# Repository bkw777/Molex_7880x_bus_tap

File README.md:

# Molex 7880x BUS TAP
Bus tap to fit between a Molex 78805 socket and a chip in a Molex 78802 carrier

More pics: https://photos.app.goo.gl/PHQ1rTQFpPRF6NSh8

Provides a connection point for a logic analyzer or oscilloscope to tap the bus between a Molex 78805 socket and a mating Molex 78802 carrier module that would normally be in the socket.

## Parts

Carrier for the small PCB: https://github.com/bkw777/Molex78802_Module/blob/master/Carrier/Molex78802_PCB_28.stl  
&nbsp;&nbsp;Some places to buy from. Select Material: Nylon, Process: SLS or MJF  
&nbsp;&nbsp;https://www.sculpteo.com/en/print/molex78802_pcb_28-18/nC7YgK6X  
&nbsp;&nbsp;https://www.pcbway.com/project/shareproject/Molex_7880x_28_PCB_Carrier_9419cd9c.html

Housing for the large PCB: [CASE/Molex_7880x_bus_tap_cover.stl](CASE/Molex_7880x_bus_tap_cover.stl)  
&nbsp;&nbsp;This one can be FDM printed.

FFC connector (x2): https://www.digikey.com/en/products/detail/amphenol-cs-fci/F52R-1A7H1-11028/11564624

FFC cable - 4" gold - Molex 0150390449 : https://www.digikey.com/en/products/detail/molex/0150390449/11581605  
FFC Cable - 6" gold - Molex 0150390453 : https://www.digikey.com/en/products/detail/molex/0150390453/11581883  
Other FFC Cables in other lengths, copper weight, plating options: https://www.digikey.com/short/pqq5pd04  

Molex 78805 socket: These are no longer made. Find me on the M100 mail list. I have some and will sell them one at a time until gone.  

Other possible solutions for the socket:  
* Once in a great while they do turn up on ebay or other places on-line:  
  https://www.dhgate.com/product/for-molex-dip28p-ic-chip-socket-silver-plated/835617844.html  
  https://www.ebay.com/itm/153988317907  
  Search "molex ic socket" and then ignore all the normal dip sockets.  
  Other search terms: 8878 28S, A78805-0518, A78805-0918, 15-29-9282, 15-41-2283  
  Or any other part number from here: https://github.com/bkw777/Molex78802_Module/blob/master/references/015299282_sd_corrected.pdf  
  Particularly detail-1, detail-10, detail-11 as those ones all have key slots at positions 1,5,9. The peg positions on the bottom don't matter because they can just be cut off.  
  (Or maybe I'll update the pcb to include drill holes in all 8 peg positions. Really any version of the socket would be better than nothing if you found any at all, just cut the missing key slots if needed.)  
* DIP-28 (or more) test clip and a standard dip-28 socket or male pin headers to connect the wires.  
  When searching for a test clip, make sure it opens wide enough for 600 mill / aka 0.6" wide dip-28, not just 300 mil.  
  https://duckduckgo.com/?t=h_&q=test+clip+dip+28+32+40+600+0.6
* Solder long wire-wrap pins in place of the socket and wedge the module between the pins.  
  https://www.digikey.com/en/products/detail/samtec-inc/ZW-16-15-F-S-225-175/6614101  
  The width of the module is a little wider than the width of the pins, so the pins would need to be bent, or change the PCB to provide a footprint with just the right spacing.  
* Change the PCB to use 2 of these: https://www.digikey.com/en/products/detail/samtec-inc/SIR1-15-L-S/10218718  
* Change the PCB to use these: https://lectronz.com/products/flexypin-pack-of-100

TODO: Design a socket that can be printed and just needs plain wire for the contacts.

Machines with this socket:  
* TRS-80/TANDY Model 100, 102, 200, 600
* Kyotronic KC-85
* Epson PX-4, PX-8
* Intermec 9440, Telexon 710, and similar hand-held teriminals
* Allen-Bradley SLC 500 programmable controllers

Cable notes:  
4" is long enough to reach out from under the nearest side to the socket on all machines.  
6" is long enough to reach the left instead of the front on a Model 200.  
8" is long enough to reach the back on a Model 100, and does still work, but might be getting marginal at this length.  
10" untested  
12" does not work

# PINOUTS
<table>
<tr> <th colspan=4>TANDY 100/102/200</th> <th width=100></th> <th colspan=4>TANDY 600 / Epson PX-4/8<br>(STANDARD MASK ROM)</th> </tr>
<tr> <td>VCC</td><td>1</td><td>28</td><td>A14</td> <td></td>  <td>NC</td><td>1</td><td>28</td><td>VCC</td> </tr>
<tr> <td>A10</td><td></td><td></td><td>/CS</td> <td></td>  <td>A12</td><td></td><td></td><td>A14</td> </tr>
<tr> <td>A7</td><td></td><td></td><td>A8</td> <td></td>  <td>A7</td><td></td><td></td><td>A13</td> </tr>
<tr> <td>A6</td><td></td><td></td><td>A9</td> <td></td>  <td>A6</td><td></td><td></td><td>A8</td> </tr>
<tr> <td>A5</td><td></td><td></td><td>A12</td> <td></td>  <td>A5</td><td></td><td></td><td>A9</td> </tr>
<tr> <td>A4</td><td></td><td></td><td>ALE</td> <td></td>  <td>A4</td><td></td><td></td><td>A11</td> </tr>
<tr> <td>A3</td><td></td><td></td><td>A13</td> <td></td>  <td>A3</td><td></td><td></td><td>/OE</td> </tr>
<tr> <td>A2</td><td></td><td></td><td>/OE</td> <td></td>  <td>A2</td><td></td><td></td><td>A10</td> </tr>
<tr> <td>A1</td><td></td><td></td><td>A11</td> <td></td>  <td>A1</td><td></td><td></td><td>/CS</td> </tr>
<tr> <td>A0</td><td></td><td></td><td>AD7</td> <td></td>  <td>A0</td><td></td><td></td><td>D7</td> </tr>
<tr> <td>AD0</td><td></td><td></td><td>AD6</td> <td></td>  <td>D0</td><td></td><td></td><td>D6</td> </tr>
<tr> <td>AD1</td><td></td><td></td><td>AD5</td> <td></td>  <td>D1</td><td></td><td></td><td>D5</td> </tr>
<tr> <td>AD2</td><td></td><td></td><td>AD4</td> <td></td>  <td>D2</td><td></td><td></td><td>D4</td> </tr>

<tr> <td>GND</td><td>14</td><td>15</td><td>AD3</td> <td></td>  <td>GND</td><td>14</td><td>15</td><td>D3</td> </tr>
</table>
<!--
|     |     |     |     |     |     |     |     |     |     |
| --- | --- | --- | --- | --- | --- | --- | --- | --- | --- |
| VCC | 1   | 28  | A14 |     |     | NC  | 1   | 28  | VCC |
| A10 |     |     | /CS |     |     | A12 |     |     | A14 |
| A7  |     |     | A8  |     |     | A7  |     |     | A13 |
| A6  |     |     | A9  |     |     | A6  |     |     | A8  |
| A5  |     |     | A12 |     |     | A5  |     |     | A9  |
| A4  |     |     | ALE |     |     | A4  |     |     | A11 |
| A3  |     |     | A13 |     |     | A3  |     |     | /OE |
| A2  |     |     | /OE |     |     | A2  |     |     | A10 |
| A1  |     |     | A11 |     |     | A1  |     |     | /CS |
| A0  |     |     | AD7 |     |     | A0  |     |     | D7  |
| AD0 |     |     | AD6 |     |     | D0  |     |     | D6  |
| AD1 |     |     | AD5 |     |     | D1  |     |     | D5  |
| AD2 |     |     | AD4 |     |     | D2  |     |     | D4  |
| GND | 14  | 15  | AD3 |     |     | GND | 14  | 15  | D3  |
-->

# GND pins work-around
This thing could really use a bunch more GND pins, both for logic analyzer probes and for a place to clip oscilloscope probe alligator clips.
Currently there is only the single GND pin which is pin 14.

For now a simple work-around that provides both extra pins for logic analyzer probe grounds and a perfect place for a scope probe alligator clip, is just a piece of single row male pin header with a wire soldered to bridge all of the posts, and a single short female-female dupont jumper to connect to the single gnd pin.

# Related
http://tandy.wiki/Molex78802_Module  
https://github.com/bkw777/M4ROM  
http://tandy.wiki/Teeprom  
http://tandy.wiki/REX

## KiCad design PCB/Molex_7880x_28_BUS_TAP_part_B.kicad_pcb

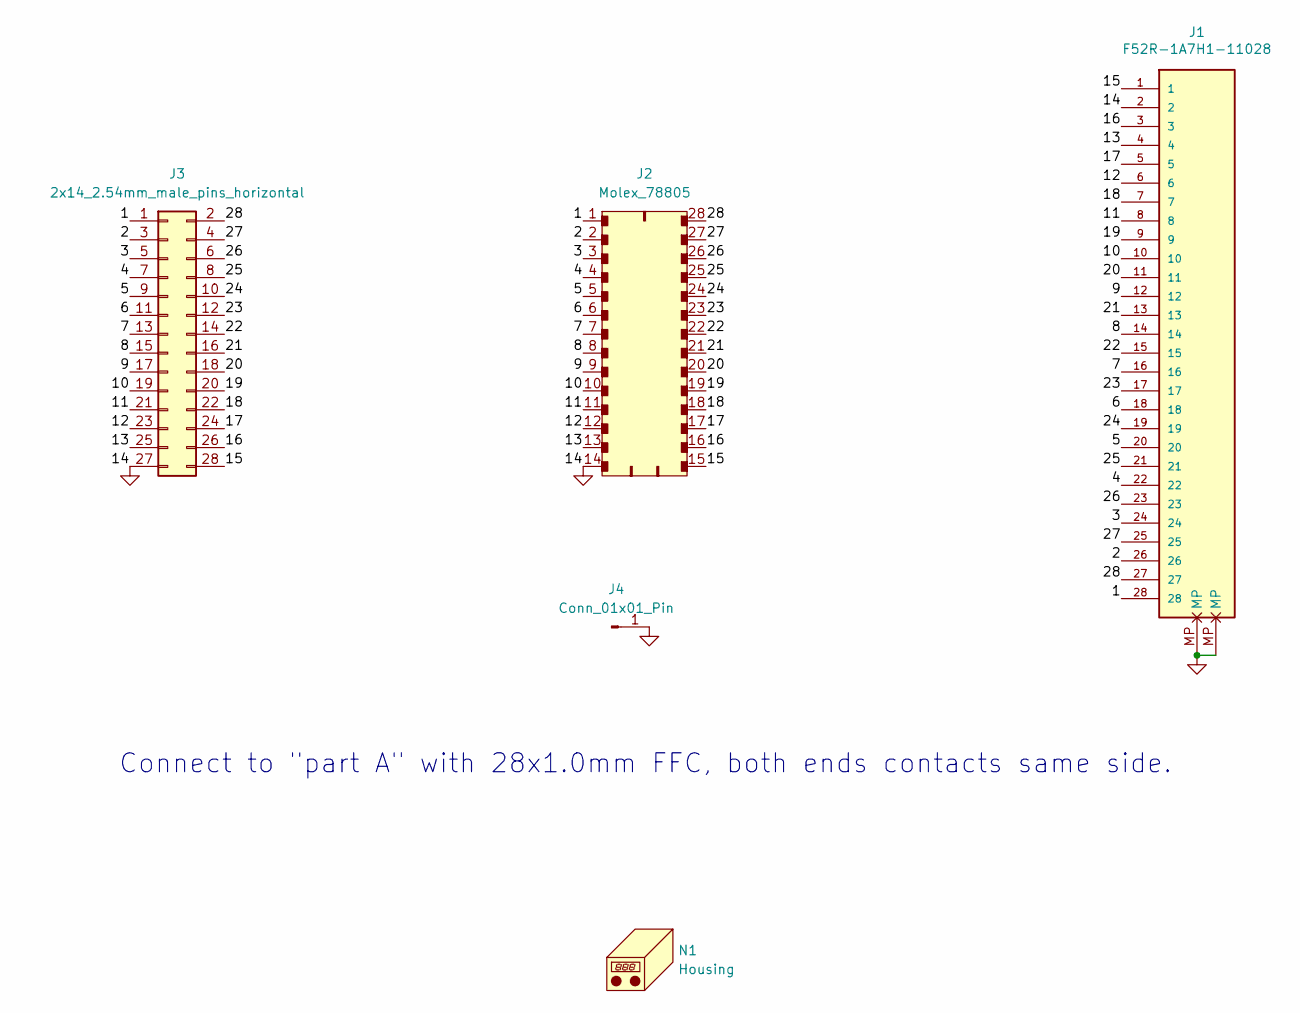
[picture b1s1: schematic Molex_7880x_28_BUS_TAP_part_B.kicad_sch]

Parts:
J1: F52R-1A7H1-11028; PARTREV A
J2: Molex_78805
J3: 2x14_2.54mm_male_pins_horizontal; PinHeader_2x14_P2.54mm_LH
J4: Conn_01x01_Pin; PinHeader_1x1_P2.54mm
N1: Housing; Molex_7880x_bus_tap_cover

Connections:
/1: J1.28, J2.1, J3.1
/2: J1.26, J2.2, J3.3
/3: J1.24, J2.3, J3.5
/4: J1.22, J2.4, J3.7
/5: J1.20, J2.5, J3.9
/6: J1.18, J2.6, J3.11
/7: J1.16, J2.7, J3.13
/8: J1.14, J2.8, J3.15
/9: J1.12, J2.9, J3.17
/10: J1.10, J2.10, J3.19
/11: J1.8, J2.11, J3.21
/12: J1.6, J2.12, J3.23
/13: J1.4, J2.13, J3.25
/15: J1.1, J2.15, J3.28
/16: J1.3, J2.16, J3.26
/17: J1.5, J2.17, J3.24
/18: J1.7, J2.18, J3.22
/19: J1.9, J2.19, J3.20
/20: J1.11, J2.20, J3.18
/21: J1.13, J2.21, J3.16
/22: J1.15, J2.22, J3.14
/23: J1.17, J2.23, J3.12
/24: J1.19, J2.24, J3.10
/25: J1.21, J2.25, J3.8
/26: J1.23, J2.26, J3.6
/27: J1.25, J2.27, J3.4
/28: J1.27, J2.28, J3.2
GND: J1.2, J1.MP, J2.14, J3.27, J4.1

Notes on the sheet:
Connect to "part A" with 28x1.0mm FFC, both ends contacts same side.

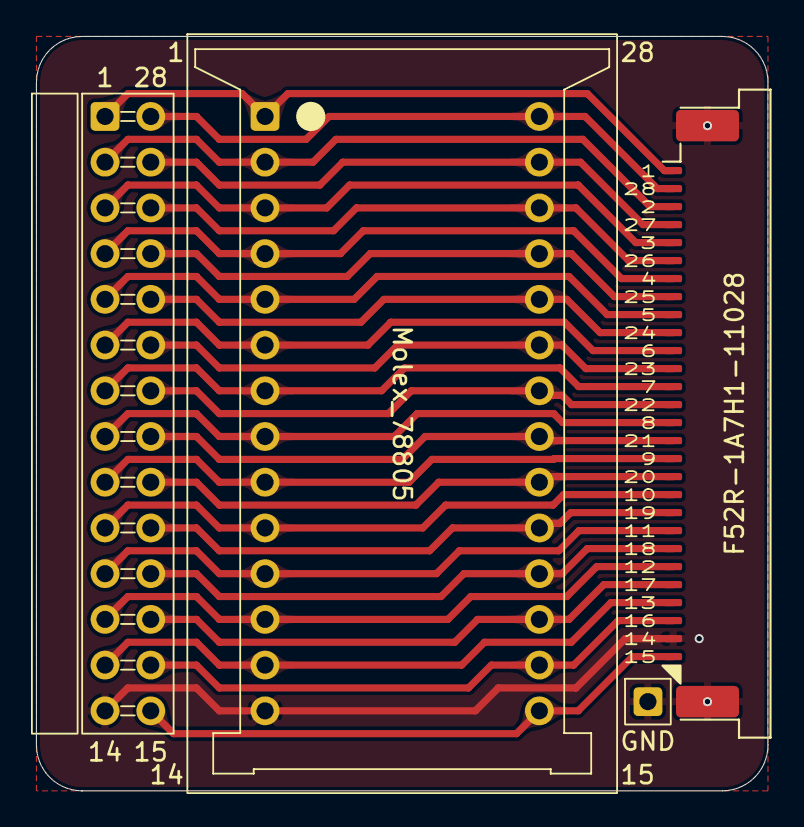
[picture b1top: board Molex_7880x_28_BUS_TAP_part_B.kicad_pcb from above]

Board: 2 copper layers, 40.6 x 41.9 mm, 5 parts (0 on the bottom side), 28 nets.

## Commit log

2024-07-31 initial
2024-09-04 add housing, add extra gnd pin
2024-09-05 readme about extra gnd hookups
2024-09-05 readme more help about special socket

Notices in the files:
PCB/Molex_7880x_28_BUS_TAP_part_B.kicad_pcb:
CC-BY-SA
